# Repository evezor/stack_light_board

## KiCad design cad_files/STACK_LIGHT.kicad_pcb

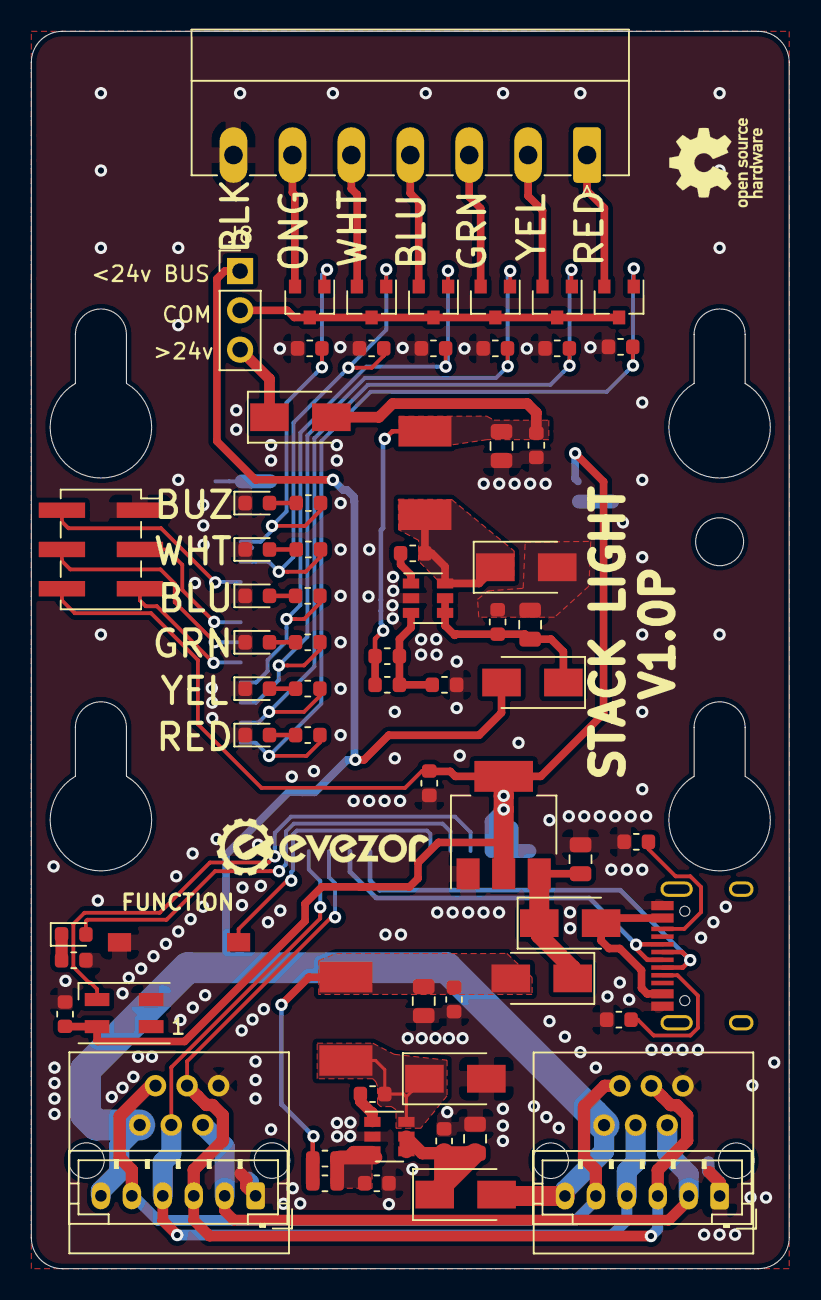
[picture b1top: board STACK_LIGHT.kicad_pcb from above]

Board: 2 copper layers, 49.0 x 80.0 mm, 71 parts (1 on the bottom side), 51 nets.

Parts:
C1, C2, C3, C5, C10, C11, C12, C13, C15: .1uF; C_0603_1608Metric
C4, C14: 4.7uF; C_0805_2012Metric
C6, C16: 22uF; C_0805_2012Metric
C8: 10uF; C_0805_2012Metric
C9: C_Small; C_0603_1608Metric
D1, D2, D4, D5, D13, D14, D15: SX35_SCHOTTKY; D_SMA
D3, D7, D8, D9, D10, D11, D12: LED; LED_0603_1608Metric
D6: SK6812MINI; LED_SK6812MINI_PLCC4_3.5x3.5mm_P1.75mm
H1: MountingHole; OLED_STANDOFF
J1: USB_C_Receptacle_USB2.0; USB_C_Receptacle_HRO_TYPE-C-31-M-12
J2, J3: RJ11; RJ11_C189747_Horizontal
J4, J5: PH; JST_PH_B6B-PH-K_1x06_P2.00mm_Vertical
J6: Conn_02x03_Odd_Even; PinSocket_2x03_P2.54mm_Vertical_SMD
J7: Conn_01x07; PhoenixContact_MC_1,5_7-G-3.81_1x07_P3.81mm_Horizontal
J8: Conn_01x03; PinHeader_1x03_P2.54mm_Vertical
L1, L2: 22uH; INDUCTOR_7.5X6.6_GCDA0630-220MC
Q1, Q2, Q3, Q4, Q5, Q6: T2N7002BK,LM‎; SOT-23
R1, R5, R20: 15k; R_0603_1608Metric
R2, R21: 82k; R_0603_1608Metric
R3, R4: 5.1k; R_0603_1608Metric
R8, R10, R12, R14, R16, R18: 1k; R_0603_1608Metric
R9, R11, R13, R15, R17, R19: 10k; R_0603_1608Metric
SW1: SW_Push; SWITCH_2x3_SMD_TACTILE_GREEN
U1, U5: SY8401ABC; SOT-23-6
U2: AMS1117-3.3; SOT-223-3_TabPin2
U3: EDGE_STM32F405_CPU_V1; EDGE_STAMP

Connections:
+3V3: C9.2, C10.1, D6.4, J6.6, U2.2, U3.1, U3.18
/BLU: Q4.1, R14.1, R15.2, U3.33
/BOOT: J6.3, U3.36
/BUZ: Q6.1, R18.1, R19.2, U3.40
/BUZZER_ONG: J7.6, Q6.2
/CAN_H: J2.3, J3.3, J4.3, J5.3, U3.26
/CAN_L: J2.4, J3.4, J4.4, J5.4, U3.27
/CC1: J1.A5, R4.1
/CC2: J1.B5, R3.1
/D+: J1.A6, J1.B6, U3.25
/D-: J1.A7, J1.B7, U3.24
/FD_H: J2.2, J3.2, J4.2, J5.2
/FD_L: J2.5, J3.5, J4.5, J5.5
/FUNCTION_BUTTON: SW1.1, U3.21
/GRN: Q3.1, R12.1, R13.2, U3.32
/HBT_LED: D3.2, U3.20
/LAYER1_RED: J7.1, Q1.2
/LAYER2_YEL: J7.2, Q2.2
/LAYER3_GRN: J7.3, Q3.2
/LAYER4_BLU: J7.4, Q4.2
/LAYER5_WHT: J7.5, Q5.2
/NEO_STATUS: D6.3, U3.19
/OLED_SCL: J6.5, U3.34
/OLED_SDA: J6.4, U3.35
/RED: Q1.1, R8.1, R9.2, U3.30
/RESET: J6.2, U3.38
/USB_VCC: D4.2, J1.A4, J1.A9, J1.B4, J1.B9
/VREG_OUT: C2.1, C5.1, C6.1, D5.2, L1.2, R2.1
/WHT: Q5.1, R16.1, R17.2, U3.39
/YEL: Q2.1, R10.1, R11.2, U3.31
GND: C3.2, C4.2, C5.2, C6.2, C8.2, C9.1, C10.2, C13.2, C14.2, C15.2, C16.2, D1.2, D6.2, D7.1, D8.1, D9.1, D10.1, D11.1, D12.1, D13.2, J1.A1, J1.A12, J1.B1, J1.B12, J2.1, J3.1, J4.1, J5.1, J6.1, J7.7, R1.1, R3.2, R4.2, R5.1, R9.1, R11.1, R13.1, R15.1, R17.1, R19.1, R20.1, SW1.2, U1.2, U2.1, U3.2, U3.17, U3.43, U5.2
unnamed: C1.1, D1.1, L1.1, U1.6
unnamed: C1.2, U1.1
unnamed: C2.2, R1.2, R2.2, U1.3
unnamed: C3.1, C4.1, D2.1, U1.4, U1.5
unnamed: C8.1, D4.1, D5.1, U2.3
unnamed: C11.1, D13.1, L2.1, U5.6
unnamed: C11.2, U5.1
unnamed: C12.1, C15.1, C16.1, D15.2, L2.2, R21.1
unnamed: C12.2, R20.2, R21.2, U5.3
unnamed: C13.1, C14.1, D14.1, U5.4, U5.5
unnamed: D3.1, R5.2
unnamed: D7.2, R8.2
unnamed: D8.2, R10.2
unnamed: D9.2, R12.2
unnamed: D10.2, R14.2
unnamed: D11.2, R16.2
unnamed: D12.2, R18.2
unnamed: D15.1, J8.3
VBUS: D2.2, D14.2, J2.6, J3.6, J4.6, J5.6, J8.1
Vdrive: J8.2, Q1.3, Q2.3, Q3.3, Q4.3, Q5.3, Q6.3

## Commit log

2020-11-15 Add message recieved script
